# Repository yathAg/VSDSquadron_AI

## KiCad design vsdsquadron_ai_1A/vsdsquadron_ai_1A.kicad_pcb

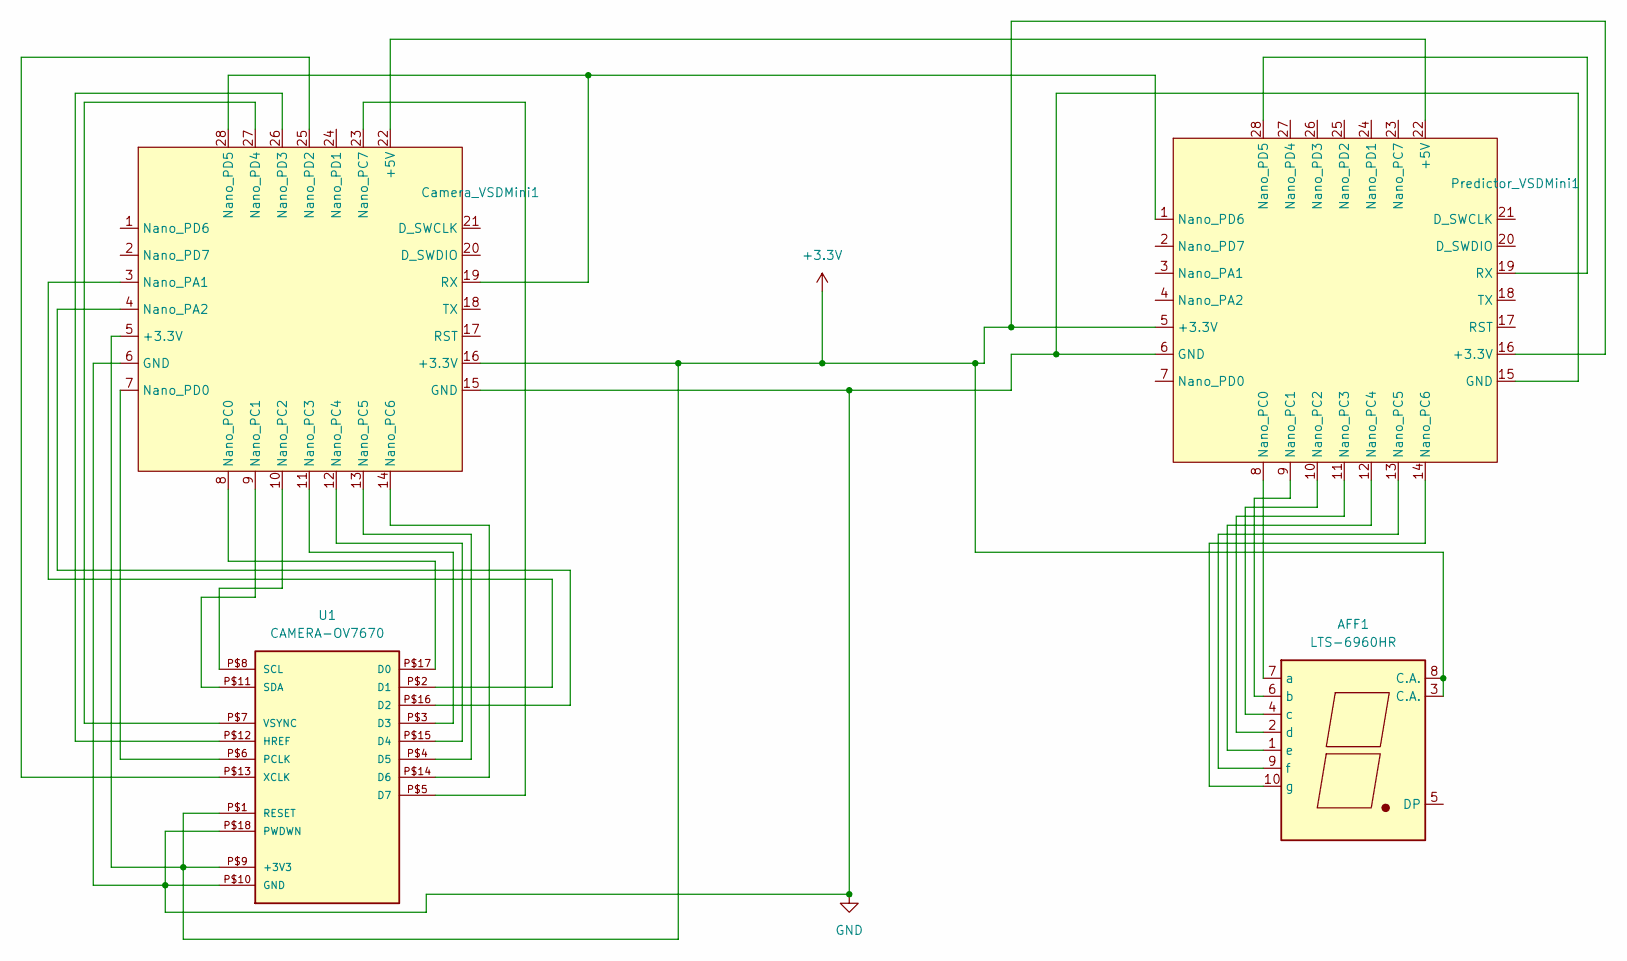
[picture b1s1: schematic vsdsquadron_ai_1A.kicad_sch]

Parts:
AFF1: LTS-6960HR; 7SegmentLED_LTS6760_LTS6780
Camera_VSDMini1: VSDSquadron Mini
Predictor_VSDMini1: VSDSquadron Mini
U1: CAMERA-OV7670; CAMERA-OV7670-DIP

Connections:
+3.3V: AFF1.3 (C.A.), AFF1.8 (C.A.), Camera_VSDMini1.5 (+3.3V), Camera_VSDMini1.16 (+3.3V), Predictor_VSDMini1.5 (+3.3V), Predictor_VSDMini1.16 (+3.3V), U1.P$1 (RESET), U1.P$9 (+3V3)
GND: Camera_VSDMini1.6 (GND), Camera_VSDMini1.15 (GND), Predictor_VSDMini1.6 (GND), Predictor_VSDMini1.15 (GND), U1.P$10 (GND), U1.P$18 (PWDWN)
unnamed: AFF1.7 (a), Predictor_VSDMini1.8 (Nano_PC0)
unnamed: AFF1.6 (b), Predictor_VSDMini1.9 (Nano_PC1)
unnamed: AFF1.4 (c), Predictor_VSDMini1.10 (Nano_PC2)
unnamed: AFF1.2 (d), Predictor_VSDMini1.11 (Nano_PC3)
unnamed: AFF1.1 (e), Predictor_VSDMini1.12 (Nano_PC4)
unnamed: AFF1.9 (f), Predictor_VSDMini1.13 (Nano_PC5)
unnamed: AFF1.10 (g), Predictor_VSDMini1.14 (Nano_PC6)
unnamed: Camera_VSDMini1.22 (+5V), Predictor_VSDMini1.22 (+5V)
unnamed: Camera_VSDMini1.3 (Nano_PA1), U1.P$2 (D1)
unnamed: Camera_VSDMini1.4 (Nano_PA2), U1.P$16 (D2)
unnamed: Camera_VSDMini1.8 (Nano_PC0), U1.P$17 (D0)
unnamed: Camera_VSDMini1.9 (Nano_PC1), U1.P$11 (SDA)
unnamed: Camera_VSDMini1.10 (Nano_PC2), U1.P$8 (SCL)
unnamed: Camera_VSDMini1.11 (Nano_PC3), U1.P$3 (D3)
unnamed: Camera_VSDMini1.12 (Nano_PC4), U1.P$15 (D4)
unnamed: Camera_VSDMini1.13 (Nano_PC5), U1.P$4 (D5)
unnamed: Camera_VSDMini1.14 (Nano_PC6), U1.P$14 (D6)
unnamed: Camera_VSDMini1.23 (Nano_PC7), U1.P$5 (D7)
unnamed: Camera_VSDMini1.7 (Nano_PD0), U1.P$6 (PCLK)
unnamed: Camera_VSDMini1.25 (Nano_PD2), U1.P$13 (XCLK)
unnamed: Camera_VSDMini1.26 (Nano_PD3), U1.P$12 (HREF)
unnamed: Camera_VSDMini1.27 (Nano_PD4), U1.P$7 (VSYNC)
unnamed: Camera_VSDMini1.19 (RX), Camera_VSDMini1.28 (Nano_PD5), Predictor_VSDMini1.1 (Nano_PD6)
unnamed: Predictor_VSDMini1.19 (RX), Predictor_VSDMini1.28 (Nano_PD5)

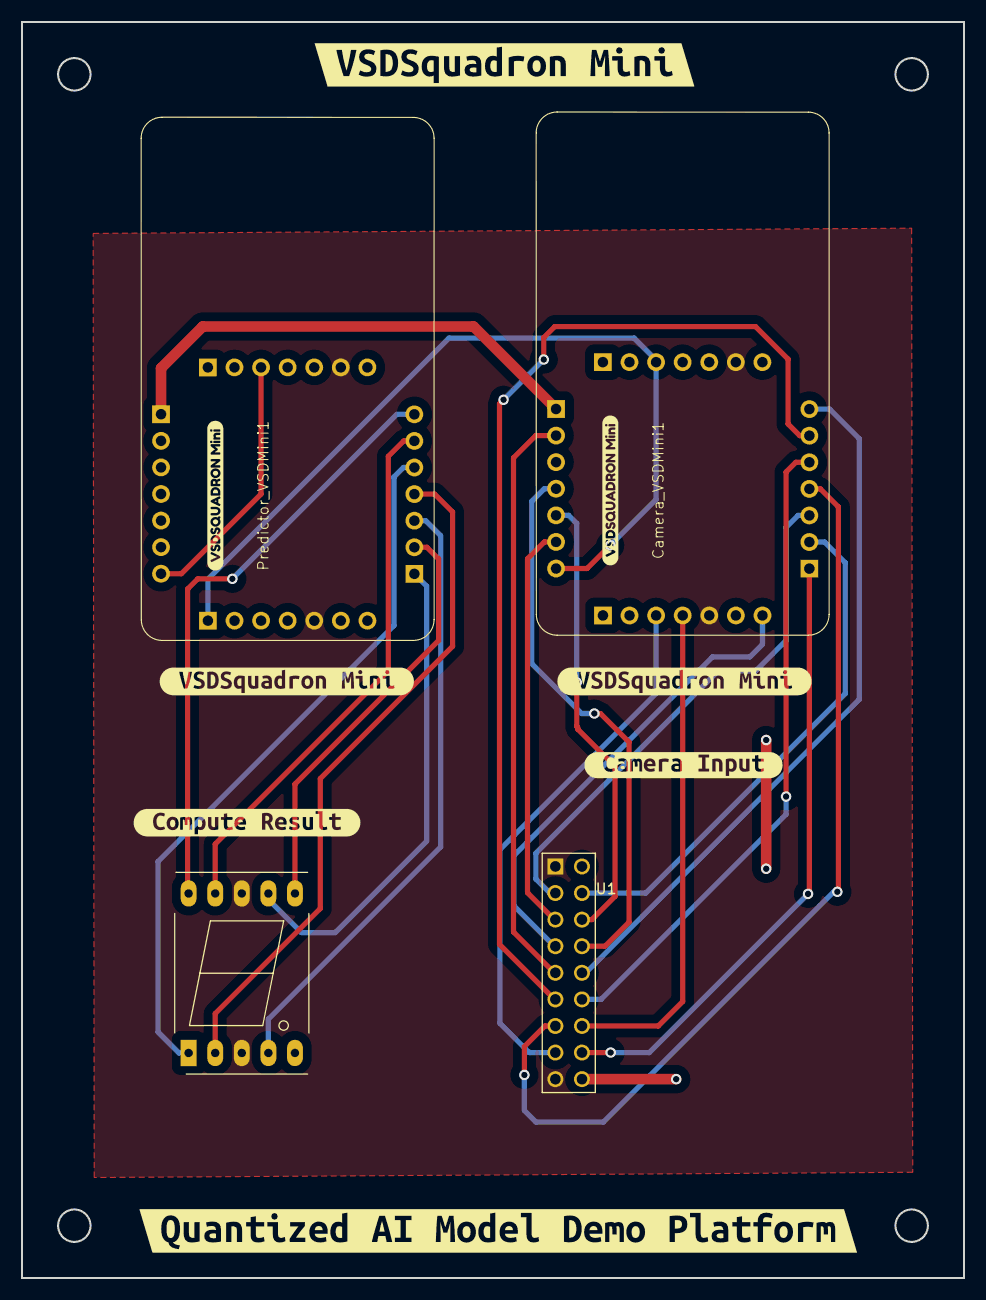
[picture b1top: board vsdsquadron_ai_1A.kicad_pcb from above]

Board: 2 copper layers, 90.0 x 120.0 mm, 10 parts (0 on the bottom side), 26 nets.

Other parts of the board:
kibuzzard-66C8A7E0: G***; kibuzzard-66C8A7E0
kibuzzard-66C8A86F: G***; kibuzzard-66C8A86F
kibuzzard-66C8A791, kibuzzard-66C8A791#2: G***; kibuzzard-66C8A791
kibuzzard-66C8AD7B: G***; kibuzzard-66C8AD7B
kibuzzard-66C8ADA8: G***; kibuzzard-66C8ADA8

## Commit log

2024-08-19 Mini Symbols
2024-08-19 Added Submodule
2024-08-23 Fianl changes
2024-08-23 edited footprint
2024-08-23 final edit
